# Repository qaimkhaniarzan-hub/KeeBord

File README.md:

# KeeBord!
Keebord is my ~60% custom keyboard that i built to fit my gaming needs! I will add a KeePad soon after this!
It has 5 rows and 15 columns of keys! (although the last column is like 1 key lol)
# Key features!
-> 59 Keys (60 if including the joystick)
-> Joystick to use as a yoke in flight sims or just general analog input that isnt a mouse
-> Raspberry PI_Pico with USB support and 40 pins
-> Custom placement, custom design, Custom firmware, and custom KiCad layout!
I personally feel like this project taught me A LOT about Kicad, Coding and just the design part of the world in general, along with the standard process of making simple objects that most don't get to see.

Initially, I was going to make a 65% keyboard with no addiitonal parts, but since i was planning on playing some rc flight simulators in preparation for a different project, i thought it;d be a GREAT idea to add a baby joystick!

## Technical Overview

### Electronics & Hardware Setup
* **Microcontroller:** Raspberry Pi Pico (RP2040) running Python-based firmware.
* **Switch Matrix:** 5 rows and 14 columns utilizing a diode-isolated matrix (COL2ROW orientation with 1N4148 diodes) to prevent ghosting across all 59 primary mechanical keys.
* **Analog Controller:** 2-axis analog thumbstick wired directly to RP2040 ADC channels (`ADC0`/`GP26` for X-axis and `ADC1`/`GP27` for Y-axis) to emulate pitch and roll axis control for simulators.
* **PCB Design:** Custom 2-layer FR-4 circuit board designed in KiCad, routing power, row/col matrix connections, and analog signals down to a single compact footprint.

### Enclosure & Ergonomics
* **Case:** Custom 3D printable shell designed in Blender and exported as standard `.STEP` assembly geometry.
* **Plate Integration:** Integrated mounting points providing rigid mounting for hot-swap switch sockets and structural support across the 300mm x 100mm footprint.

---

## How to Use KeeBord

1. **Plugging In:** Connect the onboard Raspberry Pi Pico to your PC via a USB-C cable.
2. **Standard Typing:** Typing functions out-of-the-box as a standard 60% mechanical layout with complete key rollover.
3. **Joystick Control:** In flight simulators or space games, map `ADC0` and `ADC1` to primary yoke or throttle axes inside your simulator keybind settings.
4. **Firmware Customization:** To remap key assignments, simply edit `firmware/code.py` using any text editor—no compiling or specialized flashed toolchains required.

---

## Bill of Materials (BOM)

| Component | Quantity | Description | Unit Price | Total Price |
| :--- | :---: | :--- | :---: | :---: |
| Custom KeeBord PCB | 1 | 2-Layer Custom Printed Circuit Board (300mm x 100mm) | $18.40 | $18.40 |
| Raspberry Pi Pico | 1 | Microcontroller Board (RP2040) | $4.00 | $4.00 |
| MX Mechanical Switches | 59 | Linear/Tactile MX Style Key Switches | $0.20 | $11.80 |
| 1N4148 Switching Diodes | 59 | Signal Diodes for Matrix Isolation | $0.02 | $1.18 |
| Analog Joystick Module | 1 | 2-Axis Thumb Joystick (Potentiometer) | $1.50 | $1.50 |
| Keycap Set | 1 | Standard 60% MX Keycap Set | $12.00 | $12.00 |
| 3D Printed Case | 1 | Custom Blender Enclosure (PLA) | $5.00 | $5.00 |
| **Total Estimated Cost** | | | | **$53.88** |

---

# thanks :)

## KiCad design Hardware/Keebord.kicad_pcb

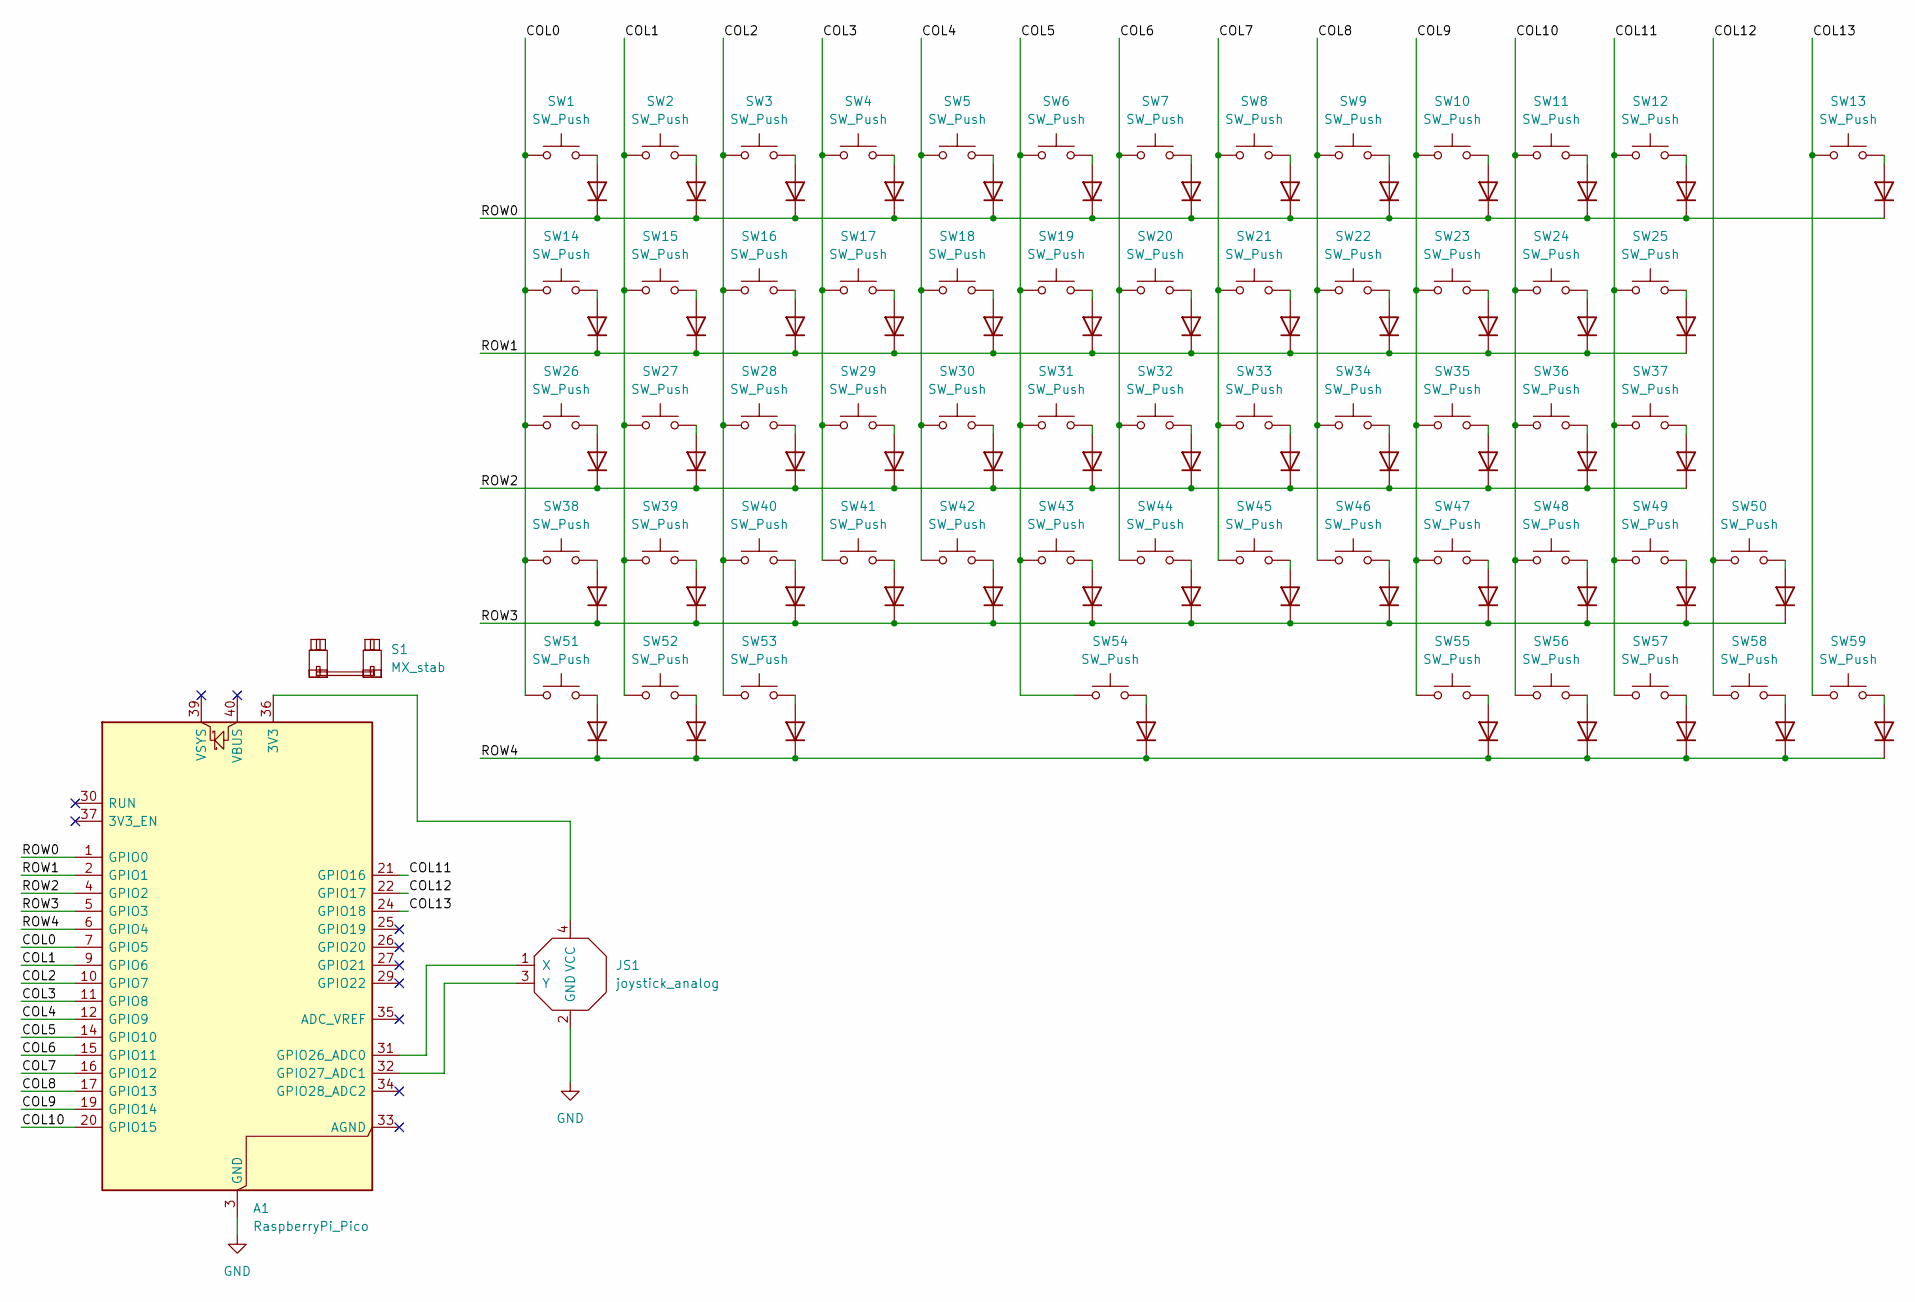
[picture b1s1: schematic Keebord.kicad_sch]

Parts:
A1: RaspberryPi_Pico; RaspberryPi_Pico_Common_THT
D1, D2, D3, D4, D5, D6, D7, D8, D9, D10, D11, D12, D13, D14, D15, D16, D17, D18, D19, D20, D21, D22, D23, D24, D25, D26, D27, D28, D29, D30, D31, D32, D33, D34, D35, D36, D37, D38, D39, D40, D41, D42, D43, D44, D45, D46, D47, D48, D49, D50, D51, D52, D53, D54, D55, D56, D57, D58, D59: 1N4148; D_DO-35_SOD27_P7.62mm_Horizontal
JS1: joystick_analog; PNT_psp1000
S1: MX_stab; STAB_MX_6u
SW1, SW2, SW3, SW4, SW5, SW6, SW7, SW8, SW9, SW10, SW11, SW12, SW13, SW14, SW15, SW16, SW17, SW18, SW19, SW20, SW21, SW22, SW23, SW24, SW25, SW26, SW27, SW28, SW29, SW30, SW31, SW32, SW33, SW34, SW35, SW36, SW37, SW38, SW39, SW40, SW41, SW42, SW43, SW44, SW45, SW46, SW47, SW48, SW49, SW50, SW51, SW52, SW53, SW54, SW55, SW56, SW57, SW58, SW59: SW_Push; SW_MX_1u

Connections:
/COL0: A1.7 (GPIO5), SW1.1, SW14.1, SW26.1, SW38.1, SW51.1
/COL1: A1.9 (GPIO6), SW2.1, SW15.1, SW27.1, SW39.1, SW52.1
/COL2: A1.10 (GPIO7), SW3.1, SW16.1, SW28.1, SW40.1, SW53.1
/COL3: A1.11 (GPIO8), SW4.1, SW17.1, SW29.1, SW41.1
/COL4: A1.12 (GPIO9), SW5.1, SW18.1, SW30.1, SW42.1
/COL5: A1.14 (GPIO10), SW6.1, SW19.1, SW31.1, SW43.1, SW54.1
/COL6: A1.15 (GPIO11), SW7.1, SW20.1, SW32.1, SW44.1
/COL7: A1.16 (GPIO12), SW8.1, SW21.1, SW33.1, SW45.1
/COL8: A1.17 (GPIO13), SW9.1, SW22.1, SW34.1, SW46.1
/COL9: A1.19 (GPIO14), SW10.1, SW23.1, SW35.1, SW47.1, SW55.1
/COL10: A1.20 (GPIO15), SW11.1, SW24.1, SW36.1, SW48.1, SW56.1
/COL11: A1.21 (GPIO16), SW12.1, SW25.1, SW37.1, SW49.1, SW57.1
/COL12: A1.22 (GPIO17), SW50.1, SW58.1
/COL13: A1.24 (GPIO18), SW13.1, SW59.1
/ROW0: A1.1 (GPIO0), D1.1 (K), D2.1 (K), D3.1 (K), D4.1 (K), D5.1 (K), D6.1 (K), D7.1 (K), D8.1 (K), D9.1 (K), D10.1 (K), D11.1 (K), D12.1 (K), D13.1 (K)
/ROW1: A1.2 (GPIO1), D14.1 (K), D15.1 (K), D16.1 (K), D17.1 (K), D18.1 (K), D19.1 (K), D20.1 (K), D21.1 (K), D22.1 (K), D23.1 (K), D24.1 (K), D25.1 (K)
/ROW2: A1.4 (GPIO2), D26.1 (K), D27.1 (K), D28.1 (K), D29.1 (K), D30.1 (K), D31.1 (K), D32.1 (K), D33.1 (K), D34.1 (K), D35.1 (K), D36.1 (K), D37.1 (K)
/ROW3: A1.5 (GPIO3), D38.1 (K), D39.1 (K), D40.1 (K), D41.1 (K), D42.1 (K), D43.1 (K), D44.1 (K), D45.1 (K), D46.1 (K), D47.1 (K), D48.1 (K), D49.1 (K), D50.1 (K)
/ROW4: A1.6 (GPIO4), D51.1 (K), D52.1 (K), D53.1 (K), D54.1 (K), D55.1 (K), D56.1 (K), D57.1 (K), D58.1 (K), D59.1 (K)
GND: A1.3 (GND), A1.8 (GND), A1.13 (GND), A1.18 (GND), A1.23 (GND), A1.28 (GND), A1.38 (GND), JS1.2 (GND)
unnamed: A1.36 (3V3), JS1.4 (VCC)
unnamed: A1.31 (GPIO26_ADC0), JS1.1 (X)
unnamed: A1.32 (GPIO27_ADC1), JS1.3 (Y)
unnamed: D1.2 (A), SW1.2
unnamed: D2.2 (A), SW2.2
unnamed: D3.2 (A), SW3.2
unnamed: D4.2 (A), SW4.2
unnamed: D5.2 (A), SW5.2
unnamed: D6.2 (A), SW6.2
unnamed: D7.2 (A), SW7.2
unnamed: D8.2 (A), SW8.2
unnamed: D9.2 (A), SW9.2
unnamed: D10.2 (A), SW10.2
unnamed: D11.2 (A), SW11.2
unnamed: D12.2 (A), SW12.2
unnamed: D13.2 (A), SW13.2
unnamed: D14.2 (A), SW14.2
unnamed: D15.2 (A), SW15.2
unnamed: D16.2 (A), SW16.2
unnamed: D17.2 (A), SW17.2
unnamed: D18.2 (A), SW18.2
unnamed: D19.2 (A), SW19.2
unnamed: D20.2 (A), SW20.2
unnamed: D21.2 (A), SW21.2
unnamed: D22.2 (A), SW22.2
unnamed: D23.2 (A), SW23.2
unnamed: D24.2 (A), SW24.2
unnamed: D25.2 (A), SW25.2
unnamed: D26.2 (A), SW26.2
unnamed: D27.2 (A), SW27.2
unnamed: D28.2 (A), SW28.2
unnamed: D29.2 (A), SW29.2
unnamed: D30.2 (A), SW30.2
unnamed: D31.2 (A), SW31.2
unnamed: D32.2 (A), SW32.2
unnamed: D33.2 (A), SW33.2
unnamed: D34.2 (A), SW34.2
unnamed: D35.2 (A), SW35.2
unnamed: D36.2 (A), SW36.2
unnamed: D37.2 (A), SW37.2
unnamed: D38.2 (A), SW38.2
unnamed: D39.2 (A), SW39.2
unnamed: D40.2 (A), SW40.2
unnamed: D41.2 (A), SW41.2
unnamed: D42.2 (A), SW42.2
unnamed: D43.2 (A), SW43.2
unnamed: D44.2 (A), SW44.2
unnamed: D45.2 (A), SW45.2
unnamed: D46.2 (A), SW46.2
unnamed: D47.2 (A), SW47.2
unnamed: D48.2 (A), SW48.2
unnamed: D49.2 (A), SW49.2
unnamed: D50.2 (A), SW50.2
unnamed: D51.2 (A), SW51.2
unnamed: D52.2 (A), SW52.2
unnamed: D53.2 (A), SW53.2
unnamed: D54.2 (A), SW54.2
unnamed: D55.2 (A), SW55.2
unnamed: D56.2 (A), SW56.2
unnamed: D57.2 (A), SW57.2
unnamed: D58.2 (A), SW58.2
unnamed: D59.2 (A), SW59.2

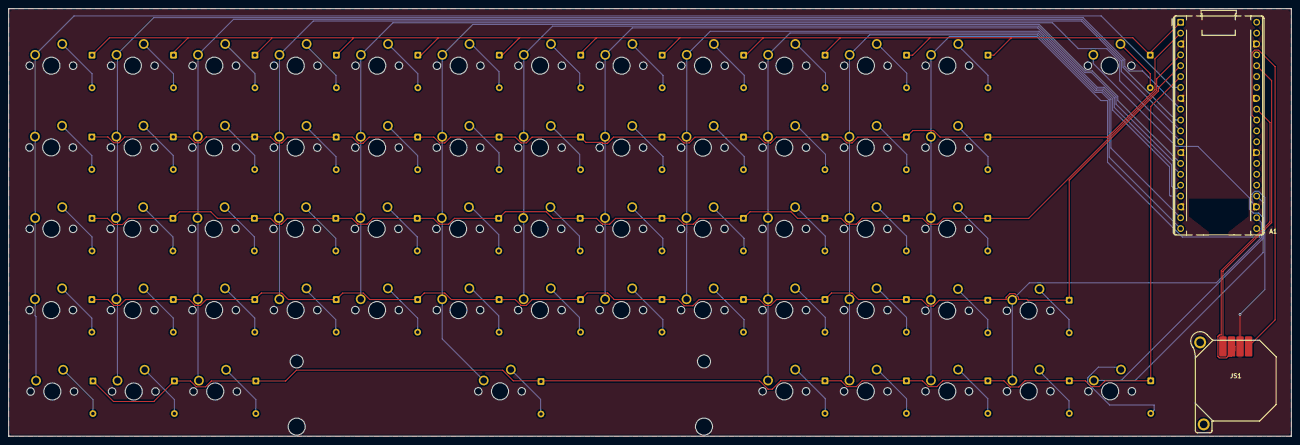
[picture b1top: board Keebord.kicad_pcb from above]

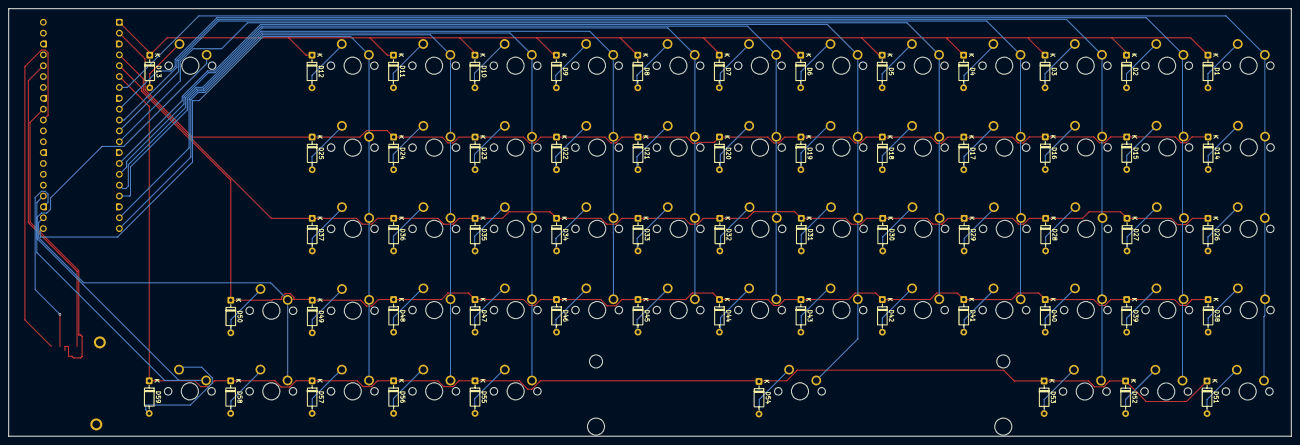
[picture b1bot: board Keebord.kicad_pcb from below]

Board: 2 copper layers, 300.0 x 100.0 mm, 121 parts (59 on the bottom side), 82 nets.

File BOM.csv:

"Id";"Designator";"Footprint";"Quantity";"Designation";"Supplier and ref";
1;"A1";"RaspberryPi_Pico_Common_THT";1;"RaspberryPi_Pico";;;
2;"D1, D2, D3, D4, D5, D6, D7, D8, D9, D10, D11, D12, D13, D14, D15, D16, D17, D18, D19, D20, D21, D22, D23, D24, D25, D26, D27, D28, D29, D30, D31, D32, D33, D34, D35, D36, D37, D38, D39, D40, D41, D42, D43, D44, D45, D46, D47, D48, D49, D50, D51, D52, D53, D54, D55, D56, D57, D58, D59";"D_DO-35_SOD27_P7.62mm_Horizontal";59;"1N4148";;;
3;"S1";"STAB_MX_P_6.25u";1;"MX_stab";;;
4;"SW1, SW2, SW3, SW4, SW5, SW6, SW7, SW8, SW9, SW10, SW11, SW12, SW13, SW14, SW15, SW16, SW17, SW18, SW19, SW20, SW21, SW22, SW23, SW24, SW25, SW26, SW27, SW28, SW29, SW30, SW31, SW32, SW33, SW34, SW35, SW36, SW37, SW38, SW39, SW40, SW41, SW42, SW43, SW44, SW45, SW46, SW47, SW48, SW49, SW50, SW51, SW52, SW53, SW54, SW55, SW56, SW57, SW58, SW59";"SW_MX_1u";59;"SW_Push";;;
